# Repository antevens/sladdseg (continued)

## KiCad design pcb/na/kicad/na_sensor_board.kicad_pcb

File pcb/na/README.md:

# NA boards (v0.7)

The North American plate's boards (single-gang box, Decora): the mains board, the sensor board and the pin board. The
mains board comes from `tools/` (`parts_na.py`, docs/DESIGN.md D-24, D-25, D-26); the sensor board and the pin board
from `../shared/tools/gen_lv.py na` with their parts in `tools/lv_parts_na.py` (D-50, D-68). Geometry shared with the
CAD comes from `cad/build123d/params.py` and `cad/build123d/na/params_na.py`. The back cover's flex, the same for both
variants, is in `../shared/README.md`.

Spacing values are design targets for human review. Nothing here is a compliance claim, and nothing on these boards
has been checked by a third party.

## Mains board (`kicad/na_mains_board_busbar.*`, fab pack in `fab/na_mains_board_busbar/`)

The NA plate's board (docs/DESIGN.md D-24, D-25, D-26, D-153): the house wiring terminal block, the emergency rocker
switch that breaks line and neutral, and the PSU fed from the switched side. The load runs in four laser-cut copper
bars soldered on the front between J1 and S1, so the board copper does not set the current (D-153; the earlier board
with the load in pours on high-CTI FR4 is dropped, D-155). Built by `gen_pcb_na.py busbar` (with
`gen_project_na.py busbar` and `gen_schematic_na.py busbar`); `tools/bars_na.py` (CAD Python) draws the bars round the
pads (`build/na_mains_board_pads.json`), checks their clearances and writes `kicad/na_mains_board_busbar_bars.json`
(their lands: copper with no solder mask) and the DXF for the laser cutter.

### Layout

Coordinates are front view in millimetres: X right, Y up toward the rocker, origin at
the board centre. F faces the plate, B faces the box.

- Board: 47 x 72 x 1.6 mm, corner radius 1.5 mm, standard FR4, 2 oz, HASL lead-free.
- Routed slot under PS1: closed, 2 mm wide, both ends round, stopping 5.5 mm above the bottom edge so the PE ring
  closes under it. Every mains copper stays 8 mm from the 5 V side by straight line, so the slot only adds.
- Bars (0.5 mm copper, tin plated), on the front, only between J1 and S1: L_IN / N_IN straight up from their pole
  (1.4 mm between the poles), then straight sides out to the rocker pad's lower corners; N_SW from J1.2 up the right
  of the rocker onto S1.2a; L_SW from J1.4 down, round J1.5 and J1.6 at 3.2 mm, up the left and over the top onto
  S1.1a. Each bar covers its rocker pad and its terminal pole's pads with a hole per pin. Narrowest bar 1.4 mm:
  0.70 mm², about 21 A at 10 °C rise (IPC-2221). Their lands are board copper of the same outline with no solder
  mask; vias inside a land are left open.
- Thin feeds in board copper (under 1 A, `BB_TRACKS`): J1.2 → B → via → RV1.2 → PS1.3; a via in the L_SW land → B →
  via → F1.1.
- PE ring: a 7 mm band round the front edge and all free copper on the back, arms to J1.1 / J1.6, 22 stitching vias
  (1.3 / 0.8 mm, 5 mm grid); continuous on B.Cu alone (the L_SW bar runs between J1.6 and the left edge on the
  front). Narrowest PE: front 2.87 mm, back 4.60 mm over the top, 2.08 mm under the slot: at 2 oz about 27 A at
  10 °C rise and about 1.5 kA for one cycle before it melts.
- 5 V area: bottom right (X 7 to 19.5, Y -33.5 to -13), GND pour on F.
- Mounting holes for the barrier's nylon standoffs (D-57), 3.2 mm, all unplated: MH1 (-21, 33.5),
  MH2 (-21, -33.5), MH3 (21, 33.5), MH4 (21, -33.5). A rule area keeps all copper 3.39 mm
  from each hole on both layers (the standoff's hex and the screw head bear on bare laminate). At MH2 / MH4
  the screw heads reach into PS1's courtyard margin, 1.35 mm clear of its body: a DRC rule allows it and
  `make check` tests the heads against the board STEP.
  Board-only footprints, not in the BOM or centroid. Mains copper keeps 1.0 mm from holes.

### Parts

| Ref | Part | MPN | Side, position | Source |
| --- | --- | --- | --- | --- |
| S1 | Marquardt rocker, DPST, PCB pins (second source: E-Switch RA412C1100, 4.8 mm tabs, D-88) | 1802.2504 | F, (0, 19.5), turned 90 degrees | Marquardt drawing 1802.2504 rev g (K-drawing 18022504.03); E-Switch RA4 datasheet |
| J1 | WAGO PCB terminal block, 6-pole, 5 mm, lever | 2604-1106 | B, pin 1 at (15.5, 8.1) and (15.5, -0.1) | <https://www.wago.com/global/pcb-terminal-blocks-and-pluggable-connectors/pcb-terminal-block/p/2604-1106> |
| PS1 | Mean Well AC-DC module, 5 V 600 mA | IRM-03-5 | B, under the slot | <https://www.meanwell.com/Upload/PDF/IRM-03/IRM-03-SPEC.PDF> |
| F1 | Schurter UMT 250 SMD fuse, T1A 250 VAC | 3403.0166.11 | F, (-14.6, -23) | <https://us.schurter.com/bundles/snceschurter/epim/_ProdPool_/newDS/en/typ_UMT_250.pdf> |
| RV1 | TDK SMD varistor 275 VAC | B72660M0271K093 (CU4032K275G2) | F, (-5.5, -22) | <https://www.farnell.com/datasheets/2921094.pdf> |
| P1, P2 | Würth WA-SMSI SMT spacer M2, 7 mm (spacer posts for the pin board, D-50, D-59, D-60) | 9774070243R | F, (9.85, -16.5), (16.65, -16.5) | <https://www.we-online.com/catalog/datasheet/9774070243R.pdf> |
| J2 | Hirose FH12 FPC connector, 6 contacts, 0.5 mm, slide lock, 5 V out to the sensor board's FFC | FH12-6S-0.5SH(55) | F, (12.7, -23.3), 0°: FFC out downwards to the barrier's slit (D-134) | <https://www.hirose.com/product/en/products/FH12/FH12-6S-0.5SH(55)/> |

S1 data from the drawing:

- Contacts 1-1a and 2-2a.
- Holes 1.3 (+0.1) mm on a 10.2 x 7 mm grid as mounted. Here plated slots 5.2 x 1.2 mm (pads 6.2 x 2.3) on
  10.2 x 7.05 mm, so the same footprint takes the E-Switch RA412C1100 (D-88): 4.8 x 0.8 tabs along x, rows 7.1
  apart, same 22 x 19.2-19.4 cutout, body 12.2 mm deep, tab tips 18.4 mm below the panel (0.6 mm through the board
  at the 16.2 seat), rocker 6.0 mm above the panel; snapped in whichever way round puts its tabs on the slots.
- Body 22 x 18.6 mm below the panel, flange 24 x 21 mm.
- PCB seat 16.2 mm below the panel face; rocker 5.3 mm above it.
- Marked ratings: ENEC 12(4) A 250 V~; UL/CSA 15 A 125-250 VAC.
- The drawing is not in the repository.

### Nets

| Net | Class | Connects |
| --- | --- | --- |
| /L_IN | Mains_L | J1.5, S1.1 |
| /L_SW | Mains_L | J1.4, S1.1a, F1.1 |
| /L_F | Mains_L | F1.2, PS1.1 (AC/L), RV1.1 |
| /N_IN | Mains_N | J1.3, S1.2 |
| /N_SW | Mains_N | J1.2, S1.2a, PS1.3 (AC/N), RV1.2 |
| /PE | PE | J1.1, J1.6, PE ring |
| +5V | SELV | PS1.16, P1, J2.2, J2.5 (mirror-symmetric pinout: an FFC flipped either way keeps the polarity) |
| GND | SELV | PS1.14, P2, J2.1, J2.3, J2.4, J2.6 |

S1 pin positions (front view): L_IN (-5.1, 19.5), L_SW (-5.1, 26.55), N_IN (5.1, 19.5),
N_SW (5.1, 26.55) (slot centres; 1802.2504 pins at 26.5, RA4 tabs at 26.6). Pins 1 / 2 lie on the body's centre line, 1a / 2a 7 mm off it (drawing
1802.2504 rev g), so the body is centred on the in pins.

Load current path: in the bars on the front, J1.5 → S1.1 (L_IN), S1.1a → J1.4 (L_SW), J1.3 → S1.2 (N_IN), S1.2a →
J1.2 (N_SW). F1 hangs off the L_SW land and the PSU's neutral off J1.2 in board copper; the fused line runs from F1.2
to PS1.1 and across to RV1.1.

### Rules

The rules are in `kicad/na_mains_board_busbar.kicad_dru`, written by `tools/gen_project_na.py busbar`.

- L to N: 3.2 mm.
- L_IN to L_SW and L_F: 3.2 mm.
- N_IN to N_SW: 3.2 mm.
- Any two different mains nets: 3.2 mm (covers switched line to fused line across F1).
- Mains to PE: 3.2 mm.

(`BB_GAP`: IEC 60664-1 creepage at the 320 V row, pollution degree 2, material group III (standard FR4), 3.2 mm,
above the OVC III clearance of 3.0 mm; D-153. Between the pins of the WAGO block its own pitch applies.)
- Mains to SELV: 8.0 mm clearance and creepage, with the routed slot.
- Mains to the PSU NC pin: 8.0 mm.
- Mains copper to board edge: 1.0 mm; other copper 0.5 mm.
- Pads of one footprint keep the part's own spacing. This is the exception for
  certified parts.

Creepage is checked only for mains to SELV. On this flat board the surface path
between copper on one layer is never shorter than the straight gap, so the 3.2 mm
targets are checked as clearance. KiCad evaluates creepage rules without the
footprint, so a per-part creepage exception cannot be written.

### Status

Done:

- Generators for the libraries, the project and rules, the schematic, the board and the
  3D envelopes.
- Placement, outline and slot, PE ring with stitching vias, pours, tracks and silkscreen.
- All nets routed.
- ERC: 0 errors, 0 warnings.
- DRC (`--severity-all --schematic-parity`): 0 violations, 0 unconnected, 0 parity issues.
- STEP model in `build/na_mains_board_busbar.step`; PCBWay order pack with the bars' DXF in
  `fab/na_mains_board_busbar/`; renders in `docs/renders/na_mains_board_busbar_*.png` (`make renders`).

Open:

- Meter-check the S1 pin numbering on a sample. The drawing's side view labels the
  pins 1a / 1 / 1b.
- RA412C1100 (D-88): which two of the RA4's three tab rows (centre, ±7.1) the DPST version has, on a sample.
  Centre and one end: fits, snapped in that way round. Both ends: the third row lands over J1 (y 12.4).
- Check the J1 pin rows on a part. They come from WAGO's 3D model (rows y 8.1 and -0.1,
  8.2 apart, D-37).
- Thermal review of the bars (narrowest 1.4 mm, 0.70 mm²) and of the PE ring at 2 oz for the branch circuit's
  fault current (D-153).
- The rocker's pin stems over the bars: on a sample, whether the 1802.2504's stems reach the board at the pads (our
  model of its drawing says they do); the bars lift it by 0.5 mm plus solder (D-153).
- The room between the board's front and the barrier for the bars: the bars are not in the CAD yet (D-153).
- WAGO 2604 pin size against the bars' 1.3 mm holes (MEASURE on a part).
- S1's body sits on the front over J1's first pin row: pad edge 1.0 mm from the body
  outline (`PAD_BODY_GAP`, checked by `make check` for every through-hole pad against the
  bodies on the other side). J1's levers overhang the S1 pins 13.9 mm or more above the
  board.
- F1 rating (T1A) is a designer's choice. Its 200 A breaking capacity at 250 VAC
  needs review against the branch circuit's prospective fault current.
- RV1 pad gap: the datasheet's D = 10.1 mm does not match B + C + B; the larger gap
  is used.
- The 22 uF output capacitor is on the sensor board at J1 (D-50).
- P1 / P2 carry the pin board and its 5 V: the WA-SBRIE studs' 5 mm male thread ends inside the 7 mm spacer, short of the board and the PSU behind it (`make check`).

### Renders

With components, then without (every trace and pour), then the copper layers (back seen from behind).

| Front | Back |
| --- | --- |
|  |  |
|  |  |
|  |  |

Dropped board (D-155), its files still in the tree until backlog item 4 removes them: `kicad/na_mains_board.*`,
`fab/na_mains_board/`, `build/na_mains_board.step` and the renders `docs/renders/na_mains_board_front.png`,
`docs/renders/na_mains_board_back.png`, `docs/renders/na_mains_board_bare_front.png`,
`docs/renders/na_mains_board_bare_back.png`, `docs/renders/na_mains_board_copper_front.png`,
`docs/renders/na_mains_board_copper_back.png`, `docs/renders/na_mains_board_iso_front.png`,
`docs/renders/na_mains_board_iso_back.png`, `docs/renders/na_mains_board_bare_iso.png`.

## Sensor board (`kicad/na_sensor_board.*`)

FR4 1.6 mm, two layers, round the barrier's collar against the wall, pressed onto its crush ribs (D-68)
(outline 66.3 × 125.9 mm, window 53.9 × 79.3 mm with a notch round each screw boss; two notches in the top edge
under the MSR-2's Boot / RST switches, which stand deeper behind its board than the CN2 stack, D-64). Seen from the
front (F faces the barrier):

- J1: Hirose FH12-6S for the 5 V FFC from the mains board's J2; GND 1, 3, 4, 6, +5V 2, 5 (the
  same mirror-symmetric pinout as J2, so the FFC's type and orientation cannot swap the polarity).
  At the bottom, (12.7, -50.0), 180°: cable in from above, over the mains board's J2 (D-134). C1 22 µF beside it.
  +5V to CN2: on the back along the bottom band, on the front up the left edge (0.35 mm, outside the keep-out) beside
  a 0.3 mm GND track, on the back across the top band.
- J2: Hirose DF40C-24DP-0.4V(51) (24 contacts, 0.4 mm) mating the MSR-2's rear connector CN2, a DF40C-24DS-0.4V(51)
  (D-154); land pattern from Hirose's DF40 catalog; contact map from Apollo's schematic; pin 1 at the left end of the
  lower row (from Apollo's boards).
- U1: SHT40 with C2 (100 nF) under the face plate's vents at the bottom.
- MK1: Knowles SPK0641HT4H-1 (top-port PDM microphone, SELECT low) at the top right, port end up under the face
  plate's sound column; U2: Analog Devices ADAU7002 (PDM to I²S, CONFIG high = I²S, WLCSP-8 0.4 mm) to its left with
  C4 (100 nF), R1 (100 kΩ I²S SD pull-down: SDATA is tristated between words) and C3 (the mic's 100 nF, C0G 1206, D-85) outside the
  column's gasket (D-83). The I²S lanes run from CN2's signal row into U2 (SD straight in on the left, WS and SCK
  under it and up its right); PDM_CLK goes to the mic on the front, PDM_DAT on the back; a +3V3 bus under the parts
  feeds the mic and C3. The mic's GND ring pads that the signal escapes enclose (5, 6) have their own vias.
- H1–H3: Würth WA-SMSI M2 L1.5 SMT spacers (9774015243R, Ø5.3 pad on a Ø3.0 unplated hole, GND)
  under the MSR-2's board, below the face plate's posts (D-68).

Copper keeps 8 mm along the wall from the box opening (rule areas: front 6.4 mm in plan, the board
edge adds 1.6; back 8.0). So the back layer only has the bands above and below the box; the right
side carries three front lanes (SCL, SDA, +3V3; 0.15 mm, 0.33 mm pitch) round the box's corner to the
SHT40, the left side a GND pour that joins the top and bottom pours. SDA, SCL and +3V3 cross the top
band on the back, under J1, to three vias above the rail; the I²S lanes stay on the front. At CN2 (D-154) every used
contact but +5V is on the lower row: the I²S lanes go down, right and up round the header's right end, SCL and SDA
down and out past the header's ends to vias, +3V3 down to a via and on the back to the mic's parts, +5V up from the
upper row to a via; GND 1 / 2 / 4 and 23 / 24 to two vias between the rows. Vias 0.45 / 0.2 mm round CN2 and U2.

**Fit-test prototype.** CN2's part, contact map and pin 1 are Apollo's (D-154: Hirose DF40C-24DS-0.4V(51) on the
MSR-2, DF40C-24DP-0.4V(51) here, 1.5 mm mated; land pattern from Hirose's DF40 catalog p. 7: pads 0.23 × 0.66 at 0.4,
rows 3.37 outside / 2.05 inside, four 0.35 × 0.66 corner bracket pads; pin 1 from the add-on's mark and the MSR-2's
traces), but CN2's position on the MSR-2 (`MSR_CN2_IN`) is a photo estimate.

## Pin board (`kicad/na_pin_board.*`, fab pack in `fab/na_pin_board/`)

FR4 0.8 mm, two layers, 14 × 12 mm, in a pocket under the barrier's pocket floor (D-53, D-60, D-79). P1 / P2: M2 pads
(Ø3.8 on a plated Ø2.2 hole, under the pan heads) over the two spacer posts at its lower corners (P1 +5V, P2 GND), held by
M2 × 5 screws, which carry the current through the WA-SBRIE studs. J1 / J2: Harwin P70-2200045 SMT
spring pins with pegs (Ø2.2 pad over a plated Ø1.2 hole; +5V above, GND below) above and between the posts, at the
back cover's pad positions. 1 mm tracks.

## 5 V FFC

Stock: GCT 05-06-A-0050-A-4-06-4-G or Würth WR-FFC 687606050002 (0.5 mm, 6 contacts, 50 mm, Type 1; D-134). Mains board J2
(cable out downwards) → the slit in the barrier's bottom wall → sensor board J1 (at its bottom, cable in from above), both
latched (FH12 slide lock), all in the plane x 12.7: a 3 mm bend up out of J2, one straight run through the slit, a 4 mm
bend over onto the sensor board. Assembly: latch J2 before fitting the mains board; press the sensor board onto the
collar's crush ribs (no screws, D-68); bend the cable to shape, slide it sideways into the slit through its notch,
latch J1.

## Regenerate

```bash
make pcb        # every board; or pcb/na/tools/build.sh for the NA boards alone
```

`tools/build.sh` writes the 3D models (`../tools/gen_3d.py`), then the mains board: `gen_libs_na.py` (libraries),
`gen_project_na.py` (project seed and DRC rules), `gen_schematic_na.py`, `gen_pcb_na.py` (board and zone fill), in
`busbar` mode, and `bars_na.py` (the bars); then the sensor board and the pin board (`../shared/tools/gen_lv.py na`).
It runs ERC and DRC on all three (reports in `build/`), exports the mains board's STEP to
`build/na_mains_board_busbar.step` and writes the PCBWay packs: `fab/na_mains_board_busbar/` (`gen_fab_na.py` writes
the BOM and the centroid, `bars_na.py` the bars' DXF; S1 and the bars are not fitted) and `fab/na_pin_board/`. The
sensor board's PCBWay files are a fit-test prototype (D-154). The dropped board's mode of the same generators still
runs (backlog item 4).

## Renders

Each board with components, without them, and its copper layers (back seen from behind). The mains board's are above.

| Sensor board, front | Sensor board, back |
| --- | --- |
|  |  |
|  |  |
|  |  |

| Pin board, front | Pin board, back |
| --- | --- |
|  |  |
|  |  |
|  |  |

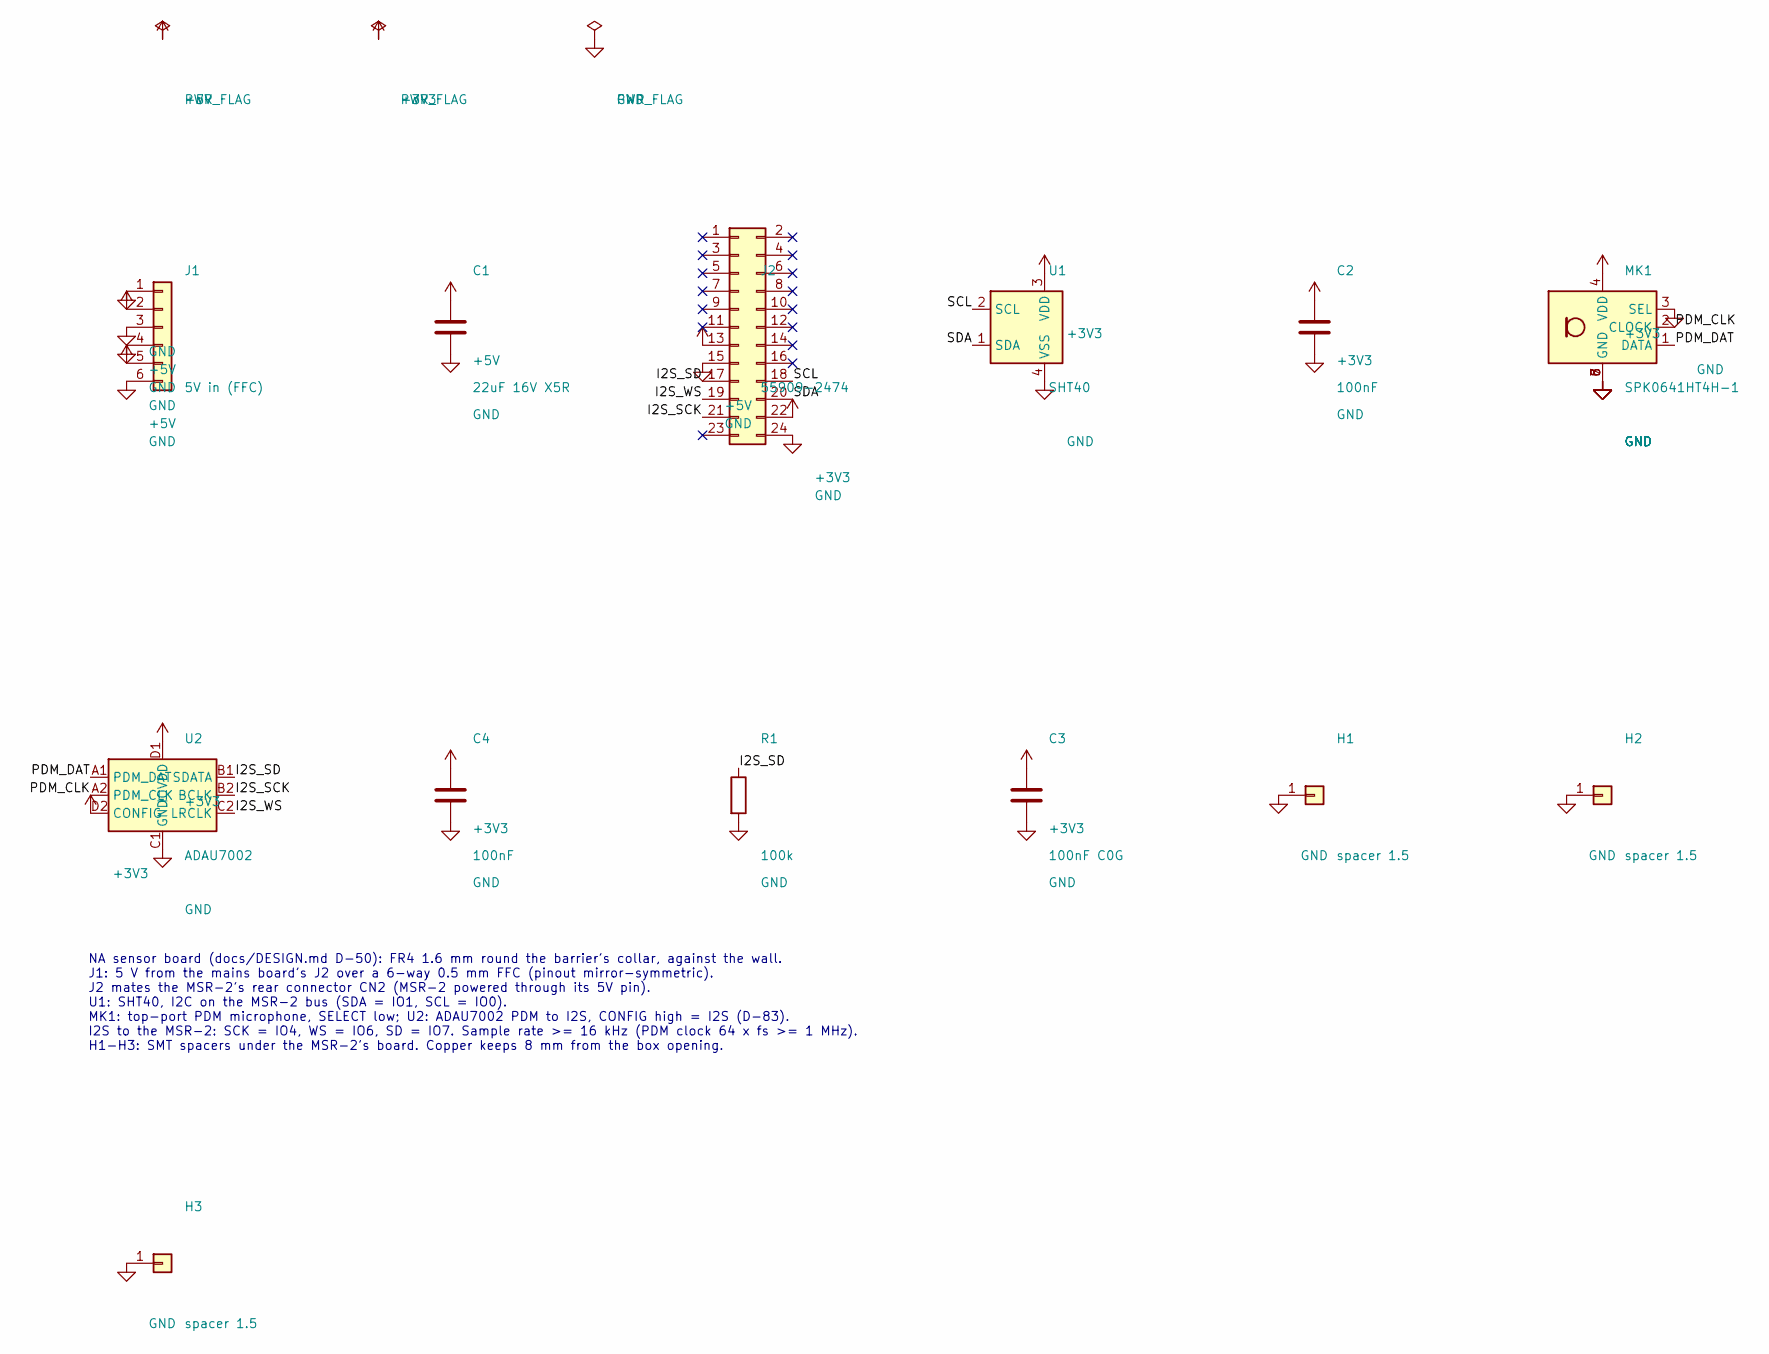
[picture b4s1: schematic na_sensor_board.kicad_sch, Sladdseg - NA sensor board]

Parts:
C1: 22uF 16V X5R; C_1206_3216Metric; MPN C1206C226M4PACTU
C2, C4: 100nF; C_0402_1005Metric; MPN 0402 X7R 100 nF 16 V
C3: 100nF C0G; C_1206_3216Metric; MPN GRM3195C1H104JA05D
H1, H2, H3: spacer 1.5; Wurth_WA-SMSI_M2_SMT_Spacer_L1.5mm; MPN 9774015243R
J1: 5V in (FFC); Hirose_FH12-6S-0.5SH_1x06-1MP_P0.50mm_Horizontal; MPN FH12-6S-0.5SH(55)
J2: 55909-2474; Molex_SlimStack_55909-2474_2x12_P0.40mm_Vertical; MPN 55909-2474
MK1: SPK0641HT4H-1; Knowles_SPK0641HT4H-1_3x4mm; MPN SPK0641HT4H-1
R1: 100k; R_0402_1005Metric; MPN 0402 1% 100 kOhm
U1: SHT40; Sensirion_DFN-4_1.5x1.5mm_P0.8mm_SHT4x_NoCentralPad; MPN SHT40-AD1B-R2
U2: ADAU7002; Analog_WLCSP-8_0.76x1.56mm_P0.4mm; MPN ADAU7002ACBZ-R7

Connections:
+3V3: C2.1, C3.1, C4.1, J2.22, MK1.4 (VDD), U1.3 (VDD), U2.D1 (IOVDD), U2.D2 (CONFIG)
+5V: C1.1, J1.2, J1.5, J2.13
/I2S_SCK: J2.21, U2.B2 (BCLK)
/I2S_SD: J2.17, R1.1, U2.B1 (SDATA)
/I2S_WS: J2.19, U2.C2 (LRCLK)
/PDM_CLK: MK1.2 (CLOCK), U2.A2 (PDM_CLK)
/PDM_DAT: MK1.1 (DATA), U2.A1 (PDM_DAT)
/SCL: J2.18, U1.2 (SCL)
/SDA: J2.20, U1.1 (SDA)
GND: C1.2, C2.2, C3.2, C4.2, H1.1, H2.1, H3.1, J1.1, J1.3, J1.4, J1.6, J2.15, J2.24, MK1.3 (SEL), MK1.5 (GND), MK1.6 (GND), MK1.7 (GND), MK1.8 (GND), R1.2, U1.4 (VSS), U2.C1 (GND)

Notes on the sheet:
NA sensor board (docs/DESIGN.md D-50): FR4 1.6 mm round the barrier's collar, against the wall. J1: 5 V from the mains board's J2 over a 6-way 0.5 mm FFC (pinout mirror-symmetric). J2 mates the MSR-2's rear connector CN2 (MSR-2 powered through its 5V pin). U1: SHT40, I2C on the MSR-2 bus (SDA = IO1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

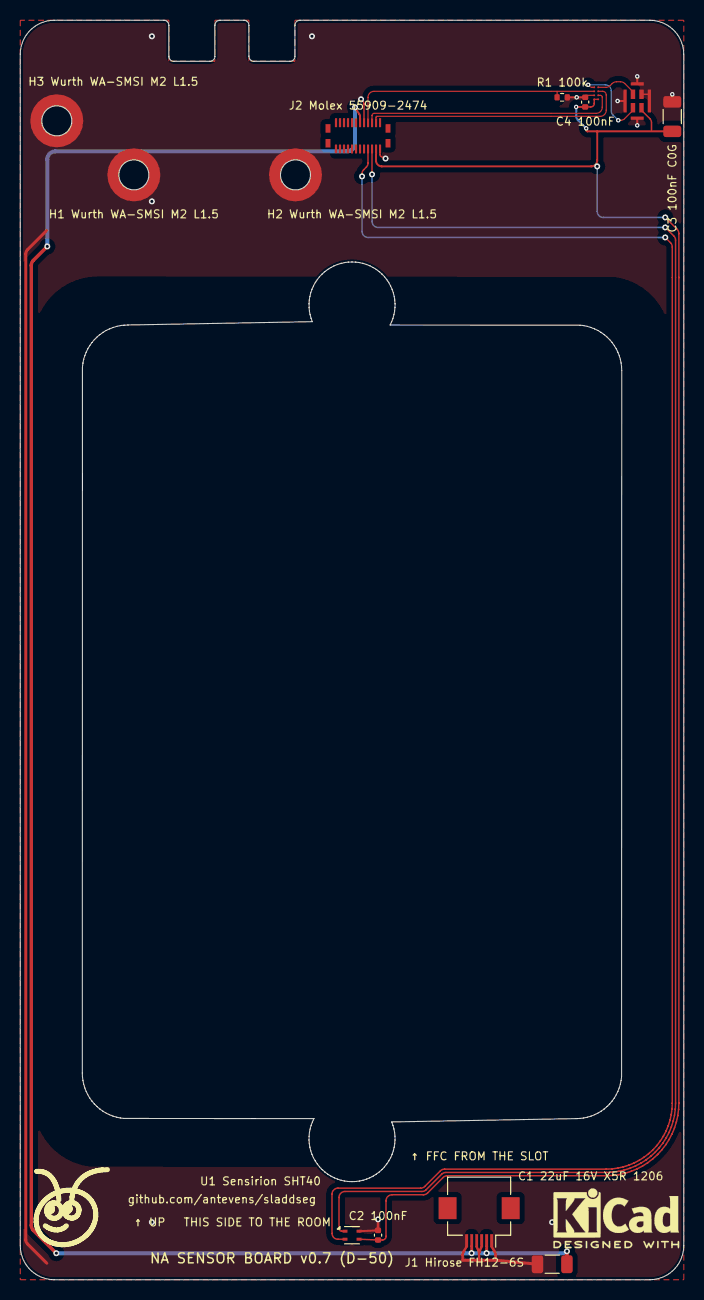
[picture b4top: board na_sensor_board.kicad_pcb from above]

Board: 2 copper layers, 66.3 x 125.8 mm, 15 parts (0 on the bottom side), 10 nets.

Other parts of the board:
LOGO1: Ant_Logo_8mm_SilkScreen
LOGO2: KiCad-Logo2_5mm_SilkScreen

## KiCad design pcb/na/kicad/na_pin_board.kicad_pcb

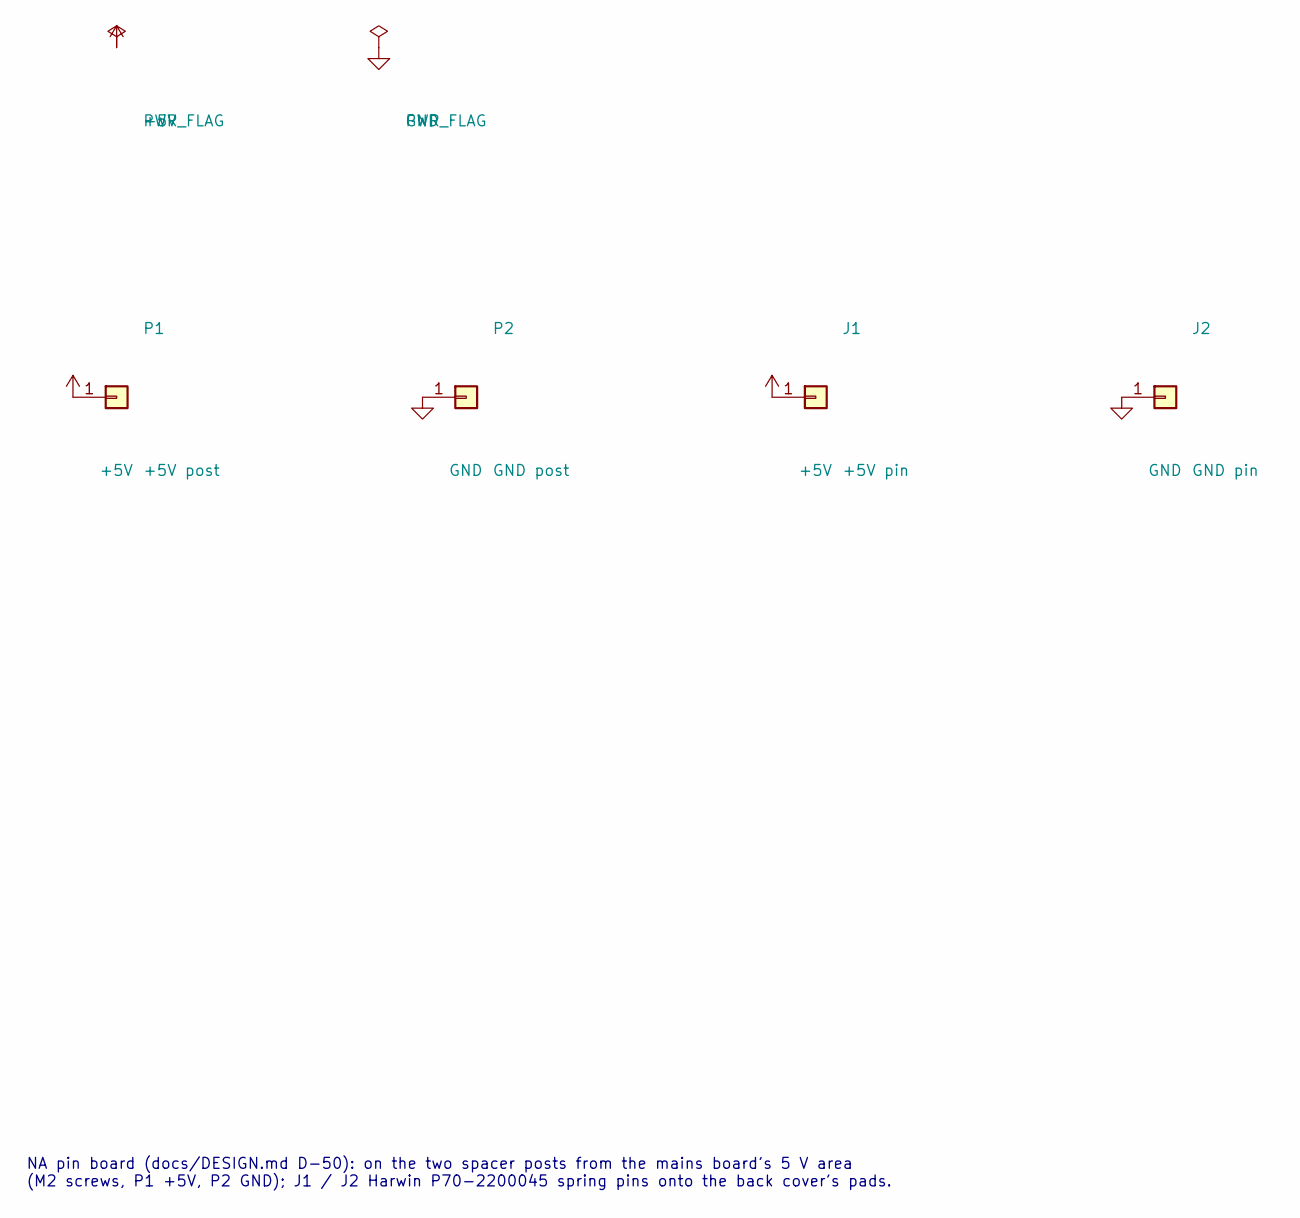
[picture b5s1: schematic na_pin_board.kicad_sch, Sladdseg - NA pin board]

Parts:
J1: +5V pin; Harwin_P70-2200045; MPN P70-2200045
J2: GND pin; Harwin_P70-2200045; MPN P70-2200045
P1: +5V post; M2_Post_Pad_D3.8mm
P2: GND post; M2_Post_Pad_D3.8mm

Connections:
+5V: J1.1, P1.1
GND: J2.1, P2.1

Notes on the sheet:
NA pin board (docs/DESIGN.md D-50): on the two spacer posts from the mains board's 5 V area (M2 screws, P1 +5V, P2 GND); J1 / J2 Harwin P70-2200045 spring pins onto the back cover's pads.

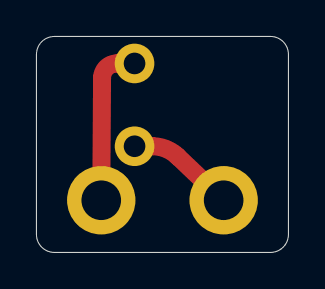
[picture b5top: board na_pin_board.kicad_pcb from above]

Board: 2 copper layers, 14.0 x 12.0 mm, 4 parts (0 on the bottom side), 2 nets.

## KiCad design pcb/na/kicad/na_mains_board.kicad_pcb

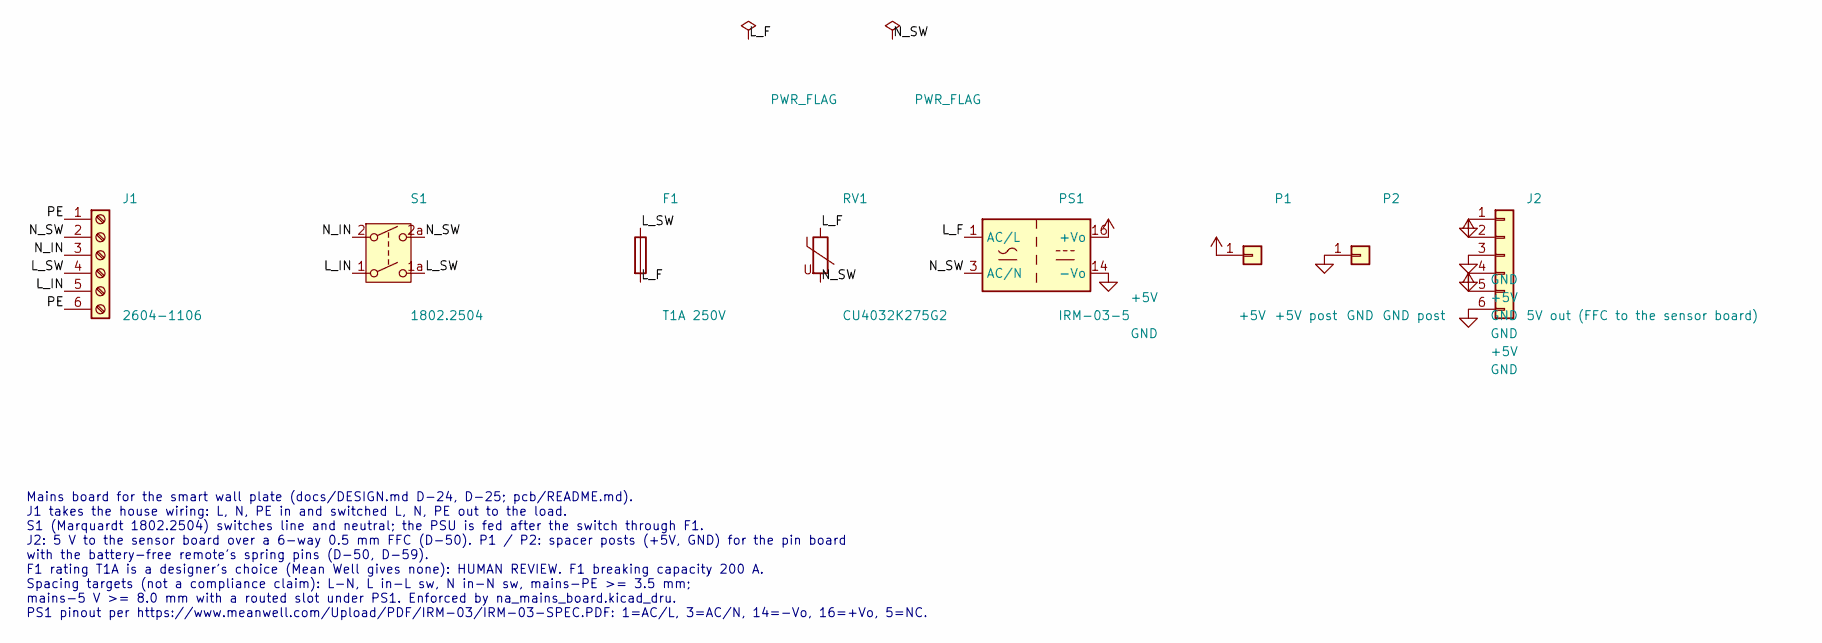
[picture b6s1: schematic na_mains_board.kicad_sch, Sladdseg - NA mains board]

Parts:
F1: T1A 250V; Fuse_Schurter_UMT250; MPN 3403.0166.11
J1: 2604-1106; WAGO_2604-1106_1x06_P5.00mm_Horizontal; MPN 2604-1106
J2: 5V out (FFC to the sensor board); Hirose_FH12-6S-0.5SH_1x06-1MP_P0.50mm_Horizontal; MPN FH12-6S-0.5SH(55)
P1: +5V post; Wurth_WA-SMSI_M2_SMT_Spacer_L7mm; MPN 9774070243R
P2: GND post; Wurth_WA-SMSI_M2_SMT_Spacer_L7mm; MPN 9774070243R
PS1: IRM-03-5; Converter_ACDC_MeanWell_IRM-03-xx_THT; MPN IRM-03-5
RV1: CU4032K275G2; Varistor_TDK_CU4032; MPN B72660M0271K093
S1: 1802.2504; Rocker_DPST_Marquardt_1802.2504_E-Switch_RA412C1100; MPN 1802.2504

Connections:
+5V: J2.2, J2.5, P1.1, PS1.16 (+Vo)
/L_F: F1.2, PS1.1 (AC/L), RV1.1
/L_IN: J1.5, S1.1
/L_SW: F1.1, J1.4, S1.1a (2)
/N_IN: J1.3, S1.2 (3)
/N_SW: J1.2, PS1.3 (AC/N), RV1.2, S1.2a (4)
/PE: J1.1, J1.6
GND: J2.1, J2.3, J2.4, J2.6, P2.1, PS1.14 (-Vo)

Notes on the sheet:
Mains board for the smart wall plate (docs/DESIGN.md D-24, D-25; pcb/README.md). J1 takes the house wiring: L, N, PE in and switched L, N, PE out to the load. S1 (Marquardt 1802.2504) switches line and neutral; the PSU is fed after the switch through F1. J2: 5 V to the sensor board over a 6-way 0.5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

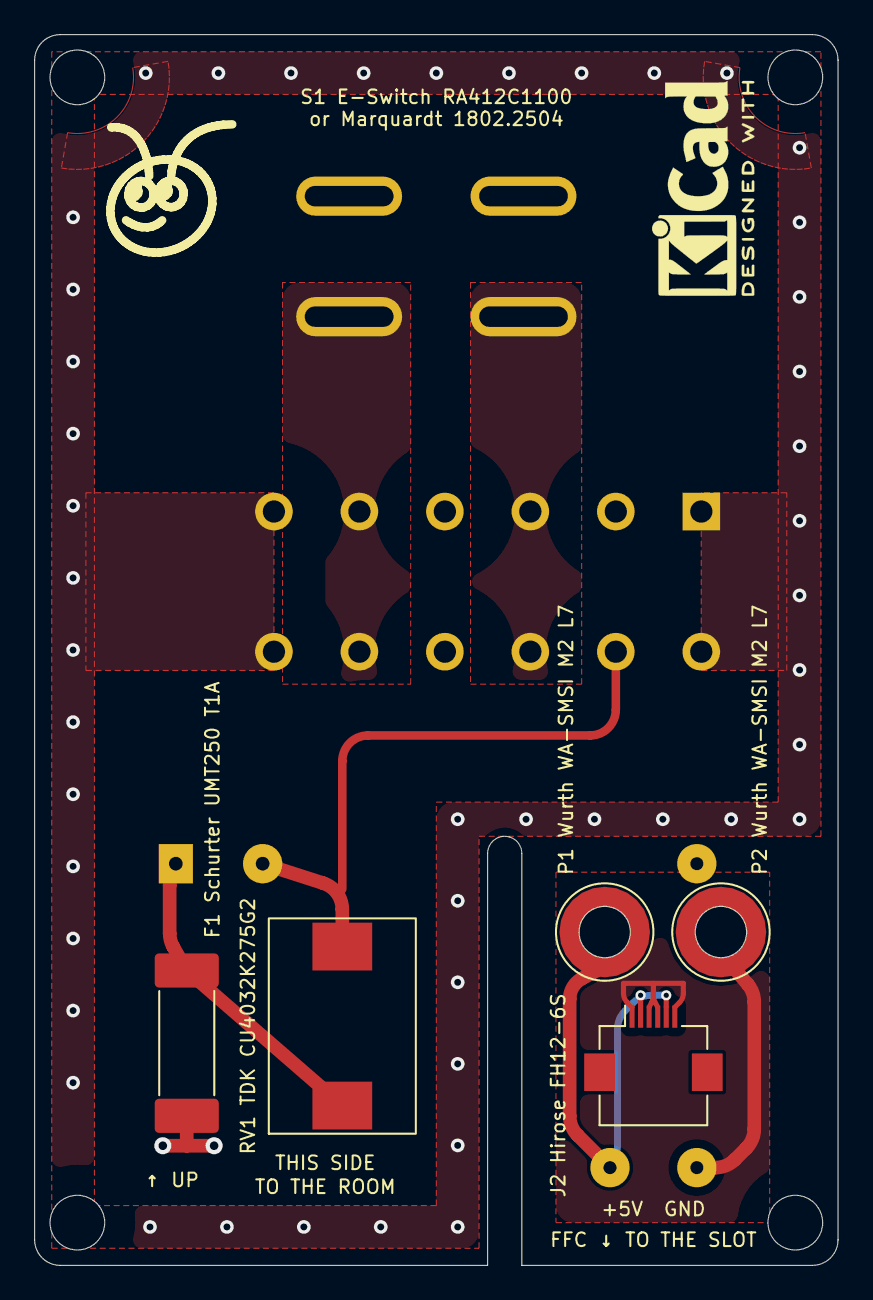
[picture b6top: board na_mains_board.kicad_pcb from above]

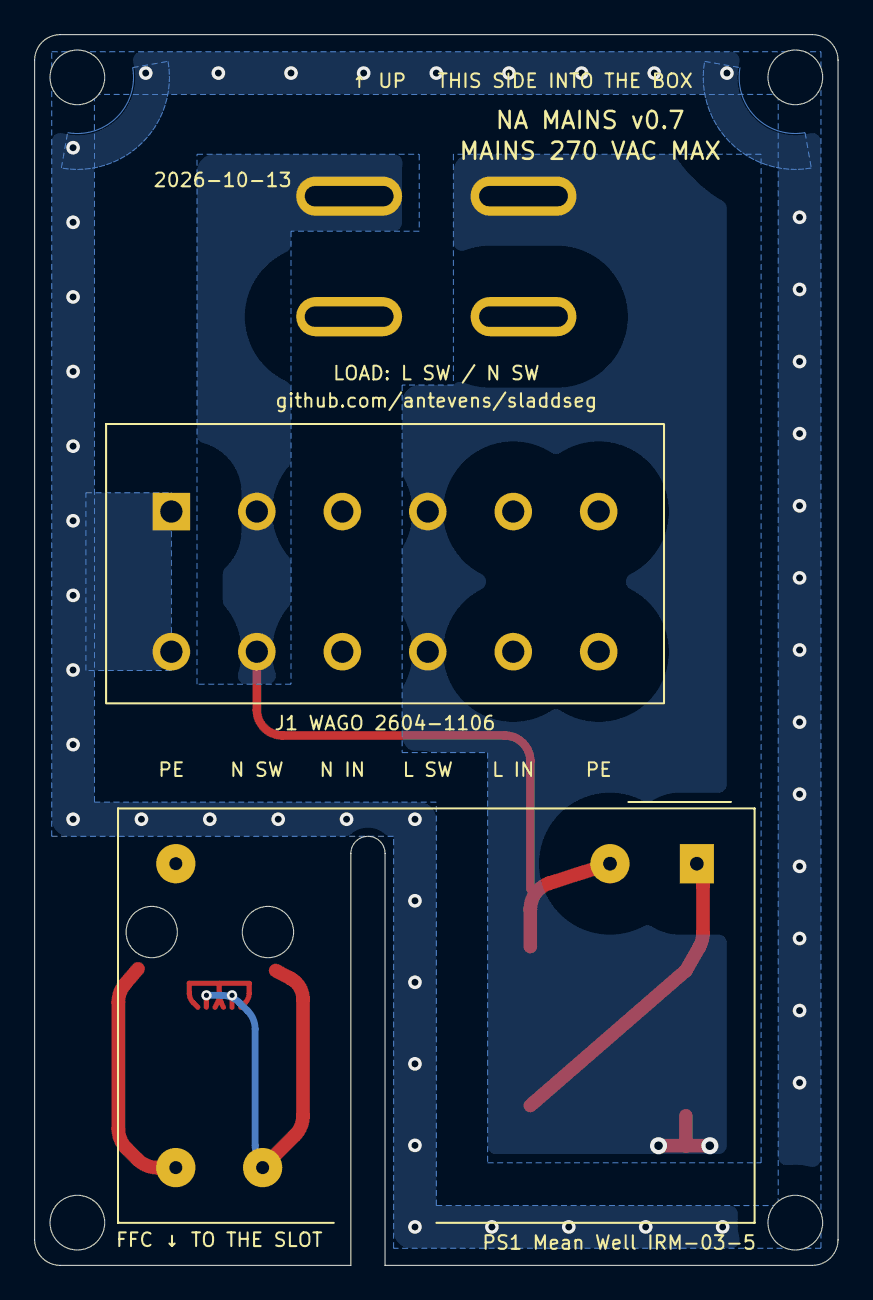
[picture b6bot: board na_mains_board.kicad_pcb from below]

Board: 2 copper layers, 47.0 x 72.0 mm, 14 parts (2 on the bottom side), 8 nets.

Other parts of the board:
LOGO1: Ant_Logo_8mm_SilkScreen
LOGO2: KiCad-Logo2_5mm_SilkScreen
MH1, MH2, MH3, MH4: MountingHole_3.2mm_M3_NPTH

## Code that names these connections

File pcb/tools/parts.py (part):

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                nets={"1": "L_F", "3": "N_SW", "16": "+5V", "14": "GND", "5": "NC5"},
                pcb=None, mfr="Mean Well", mpn="IRM-03-5",
                desc="AC-DC module 85-305 VAC in, 5 V 600 mA, 37x24x15 mm", ds=IRM_DS),
    "F1": dict(label="Schurter UMT250 T1A", sym="Fuse", fp=FP_FUSE, value="T1A 250V", nets={"1": "L_SW", "2": "L_F"},
               pcb=(-14.6, -23.0, 90, "F"), mfr="Schurter", mpn="3403.0166.11",
               desc="SMD fuse UMT 250, time-lag 1 A 250 VAC. Rating is a designer's choice: human review",
               ds=UMT_DS),
    "RV1": dict(label="TDK CU4032K275G2", sym="Varistor", fp=FP_MOV, value="CU4032K275G2", nets={"1": "L_F", "2": "N_SW"},
                pcb=(-5.5, -22.0, 90, "F"), mfr="TDK", mpn="B72660M0271K093",
                desc="SMD varistor SIOV-CU4032K275G2K1, 275 VAC", ds=CU_DS),
    # spacer posts for the battery-free remote's spring pins (D-50): the riser board screws onto them
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    # in-pins (both J1 rows) straight up on the front
    ("L_IN", "F.Cu", [(-9.0, -2.0), (-1.5, -2.0), (-1.5, 21.5), (-9.0, 21.5)]),
    ("N_IN", "F.Cu", [(2.0, -2.0), (8.5, -2.0), (8.5, 21.5), (2.0, 21.5)]),
    # switched neutral: right of the N_IN pin, over the top to S1.2a (back)
    ("N_SW", "B.Cu", [(8.5, -2.0), (14.0, -2.0), (14.0, 29.0), (1.0, 29.0), (1.0, 24.5), (8.5, 24.5)]),
    # switched line (back): up from J1.4 into the band between J1's upper pin row and the rocker's in pins, left past
    # J1.5 / S1.1, up the left side to S1.1a; also down from J1.4 under J1 and up the left edge (in parallel), feeding F1
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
